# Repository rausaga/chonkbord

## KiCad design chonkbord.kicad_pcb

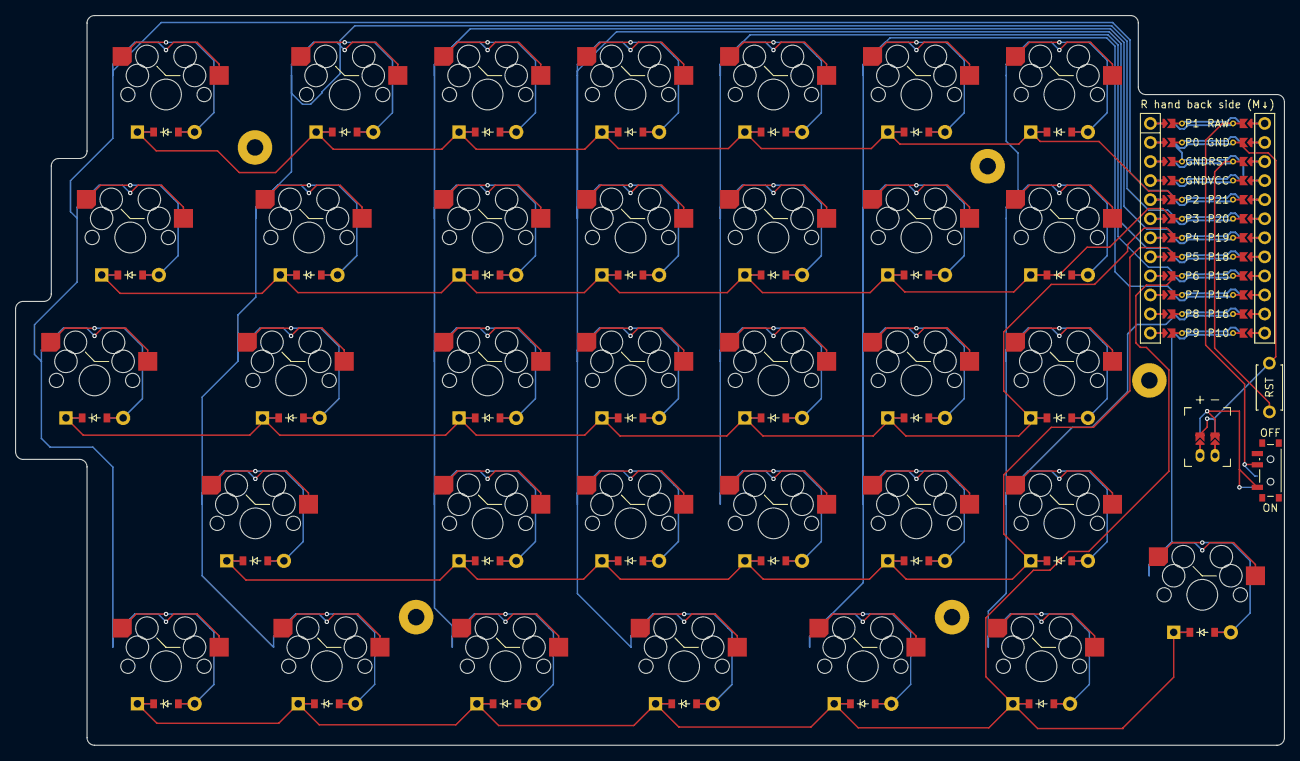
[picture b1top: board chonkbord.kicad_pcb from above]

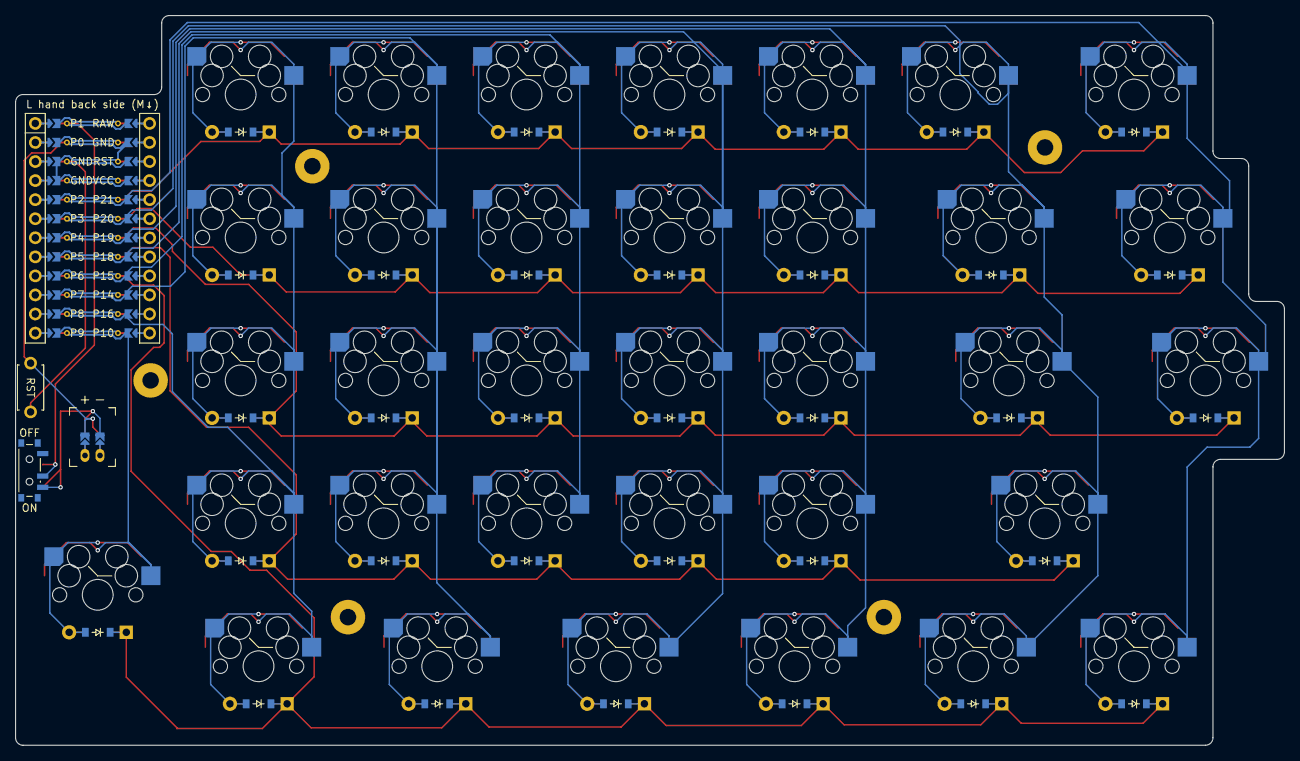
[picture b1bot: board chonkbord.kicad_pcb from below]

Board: 2 copper layers, 169.1 x 97.2 mm, 77 parts (34 on the bottom side), 53 nets.

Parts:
D1, D2, D3, D4, D5, D6, D7, D8, D9, D10, D11, D12, D13, D14, D15, D16, D17, D18, D19, D20, D21, D22, D23, D24, D25, D26, D27, D28, D29, D30, D31, D32, D33, D34: diode_tht_sod123
JST1: battery_connector_jst_ph_2
MCU1: mcu_nice_nano
MH1, MH2, MH3, MH4, MH5: mounting_hole_npth
PWR1: power_switch_smd_side
RST1: reset_switch_tht_top
S1, S2, S3, S4, S5, S6, S7, S8, S9, S10, S11, S12, S13, S14, S15, S16, S17, S18, S19, S20, S21, S22, S23, S24, S25, S26, S27, S28, S29, S30, S31, S32, S33, S34: switch_mx

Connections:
BAT_P: JST1.1, PWR1.1, PWR1.3
GND: JST1.2, MCU1.102, MCU1.121, MCU1.122, RST1.2
JST1_1: JST1.11, JST1.21, JST1.31
JST1_2: JST1.12, JST1.22, JST1.32
P2: D4.1, D9.1, D14.1, D19.1, D23.1, D28.1, D33.1, MCU1.120
P3: D3.1, D8.1, D13.1, D18.1, D22.1, D27.1, D32.1, MCU1.119
P4: D2.1, D7.1, D12.1, D17.1, D21.1, D26.1, D31.1, MCU1.118
P5: D6.1, D11.1, D16.1, D20.1, D25.1, D30.1, MCU1.117
P6: D1.1, D5.1, D10.1, D15.1, D24.1, D29.1, D34.1, MCU1.116
P10: MCU1.112, S34.1
P14: MCU1.110, S24.1, S25.1, S26.1, S27.1, S28.1
P15: MCU1.109, S20.1, S21.1, S22.1, S23.1
P16: MCU1.111, S29.1, S30.1, S31.1, S32.1, S33.1
P18: MCU1.108, S15.1, S16.1, S17.1, S18.1, S19.1
P19: MCU1.107, S10.1, S11.1, S12.1, S13.1, S14.1
P20: MCU1.106, S5.1, S6.1, S7.1, S8.1, S9.1
P21: MCU1.105, S1.1, S2.1, S3.1, S4.1
RAW: MCU1.101, PWR1.2
RST: MCU1.103, RST1.1
c0_r0: D4.2, S4.2
c0_r1: D3.2, S3.2
c0_r2: D2.2, S2.2
c0_r4: D1.2, S1.2
c1_r0: D9.2, S9.2
c1_r1: D8.2, S8.2
c1_r2: D7.2, S7.2
c1_r3: D6.2, S6.2
c1_r4: D5.2, S5.2
c2_r0: D14.2, S14.2
c2_r1: D13.2, S13.2
c2_r2: D12.2, S12.2
c2_r3: D11.2, S11.2
c2_r4: D10.2, S10.2
c3_r0: D19.2, S19.2
c3_r1: D18.2, S18.2
c3_r2: D17.2, S17.2
c3_r3: D16.2, S16.2
c3_r4: D15.2, S15.2
c4_r0: D23.2, S23.2
c4_r1: D22.2, S22.2
c4_r2: D21.2, S21.2
c4_r3: D20.2, S20.2
c5_r0: D28.2, S28.2
c5_r1: D27.2, S27.2
c5_r2: D26.2, S26.2
c5_r3: D25.2, S25.2
c5_r4: D24.2, S24.2
c6_r0: D33.2, S33.2
c6_r1: D32.2, S32.2
c6_r2: D31.2, S31.2
c6_r3: D30.2, S30.2
c6_r4: D29.2, S29.2
c7_r4: D34.2, S34.2
